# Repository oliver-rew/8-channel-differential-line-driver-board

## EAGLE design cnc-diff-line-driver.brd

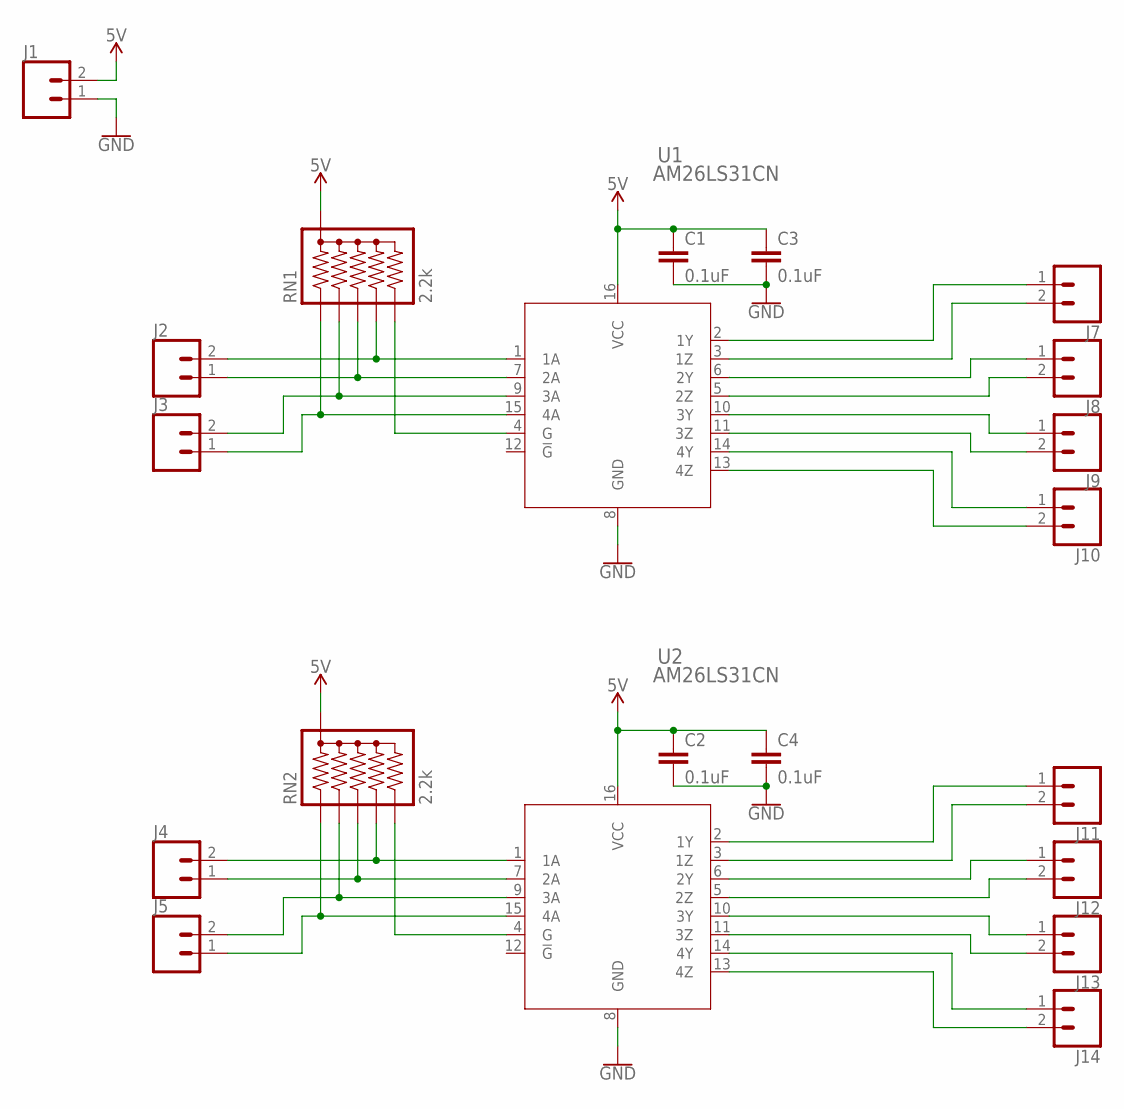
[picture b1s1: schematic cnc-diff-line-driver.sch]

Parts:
C1, C2, C3, C4: 0.1uF; CAP-PTH-SMALL-KIT
J1, J2, J3, J4, J5, J7, J8, J9, J10, J11, J12, J13, J14: PHOENIX_CON_5.08MM_SCREW_1888687; SCREWTERMINAL-5MM-2
RN1, RN2: 2.2k; RPACK-SIP-PTH-5
U1, U2: AM26LS31CN; N16

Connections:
5V: C1.1, C2.1, C3.1, C4.1, J1.2, RN1.P$1 (1), RN2.P$1 (1), U1.16 (VCC), U2.16 (VCC)
GND: C1.2, C2.2, C3.2, C4.2, J1.1, U1.8 (GND), U2.8 (GND)
unnamed: J2.2, RN1.P$5 (5), U1.1 (1A)
unnamed: J2.1, RN1.P$4 (4), U1.7 (2A)
unnamed: J3.2, RN1.P$3 (3), U1.9 (3A)
unnamed: J3.1, RN1.P$2 (2), U1.15 (4A)
unnamed: RN1.P$6 (6), U1.4 (G)
unnamed: J8.2, U1.5 (2Z)
unnamed: J8.1, U1.6 (2Y)
unnamed: J7.2, U1.3 (1Z)
unnamed: J7.1, U1.2 (1Y)
unnamed: J9.1, U1.10 (3Y)
unnamed: J9.2, U1.11 (3Z)
unnamed: J10.1, U1.14 (4Y)
unnamed: J10.2, U1.13 (4Z)
unnamed: J4.2, RN2.P$5 (5), U2.1 (1A)
unnamed: J4.1, RN2.P$4 (4), U2.7 (2A)
unnamed: J5.2, RN2.P$3 (3), U2.9 (3A)
unnamed: J5.1, RN2.P$2 (2), U2.15 (4A)
unnamed: RN2.P$6 (6), U2.4 (G)
unnamed: J12.2, U2.5 (2Z)
unnamed: J12.1, U2.6 (2Y)
unnamed: J11.2, U2.3 (1Z)
unnamed: J11.1, U2.2 (1Y)
unnamed: J13.1, U2.10 (3Y)
unnamed: J13.2, U2.11 (3Z)
unnamed: J14.1, U2.14 (4Y)
unnamed: J14.2, U2.13 (4Z)

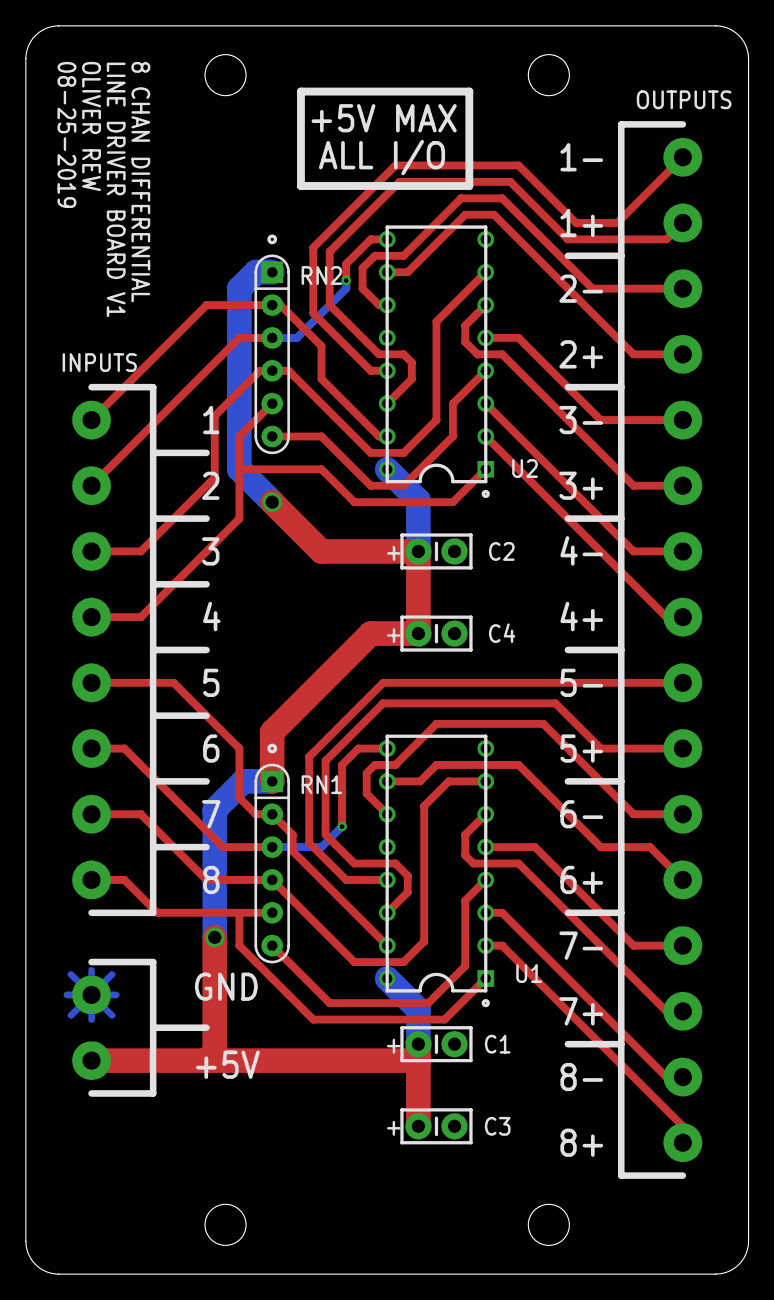
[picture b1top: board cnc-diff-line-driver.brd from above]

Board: 2 copper layers, 55.9 x 96.5 mm, 21 parts (0 on the bottom side), 28 nets.

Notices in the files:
parts and their libraries:
SparkFun-Capacitors: Licensing: Creative Commons ShareAlike 4.0 International - https://creativecommons.org/licenses/by-sa/4.0
